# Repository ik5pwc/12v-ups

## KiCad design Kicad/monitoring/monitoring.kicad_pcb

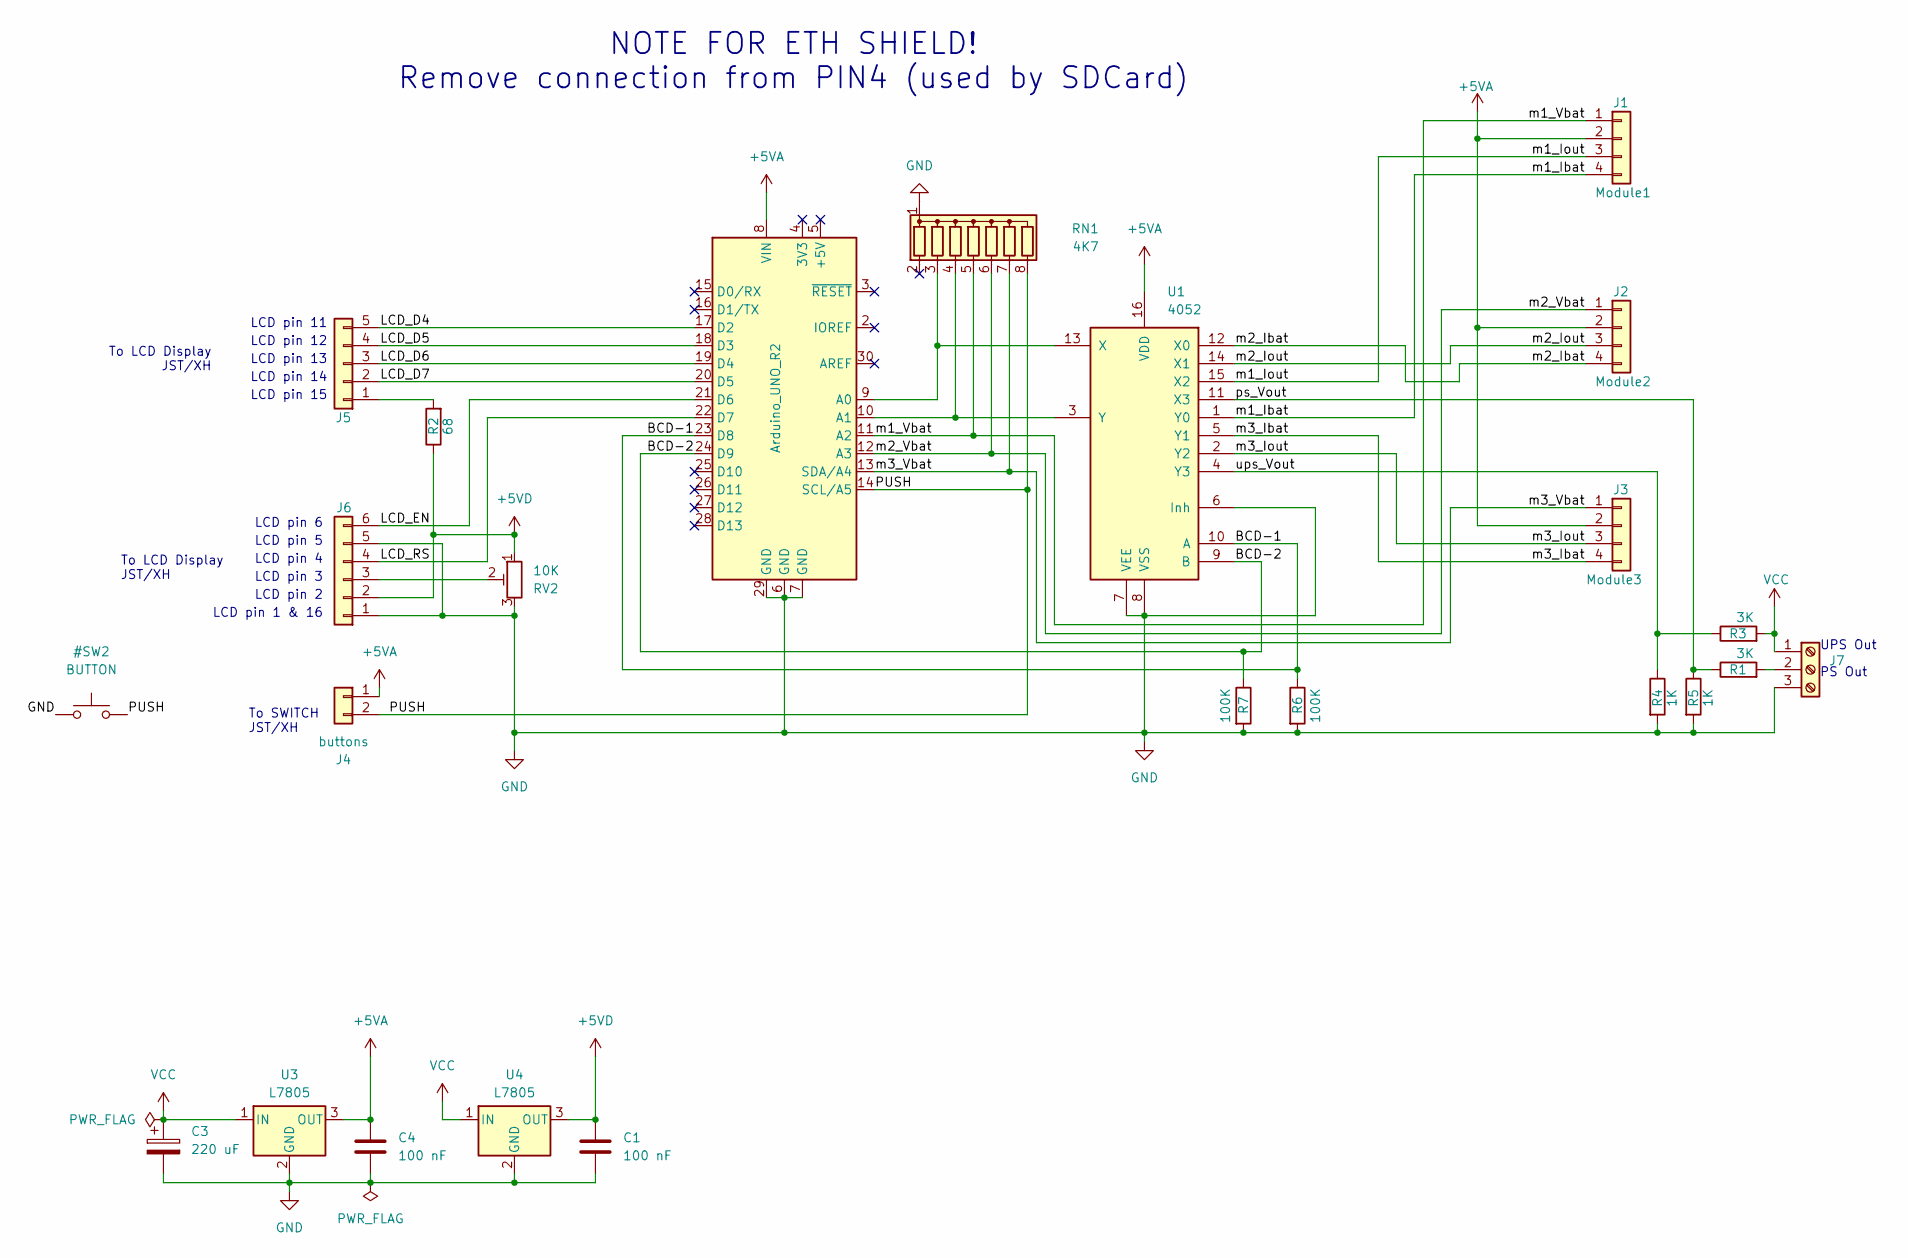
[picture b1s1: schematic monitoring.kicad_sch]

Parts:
A1: Arduino_UNO_R2
C1, C4: 100 nF; C_Disc_D4.7mm_W2.5mm_P5.00mm
C3: 220 uF; CP_Radial_D10.0mm_P5.00mm
J1: Module1; JST_XH_B4B-XH-A_1x04_P2.50mm_Vertical
J2: Module2; JST_XH_B4B-XH-A_1x04_P2.50mm_Vertical
J3: Module3; JST_XH_B4B-XH-A_1x04_P2.50mm_Vertical
J4: buttons; JST_XH_B2B-XH-A_1x02_P2.50mm_Vertical
J5: Display; JST_XH_B5B-XH-A_1x05_P2.50mm_Vertical
J6: Display; JST_XH_B6B-XH-A_1x06_P2.50mm_Vertical
J7: DC_in_outout; TerminalBlock_bornier-3_P5.08mm
R1, R3: 3K; R_Axial_DIN0204_L3.6mm_D1.6mm_P7.62mm_Horizontal
R2: 68; R_Axial_DIN0204_L3.6mm_D1.6mm_P7.62mm_Horizontal
R4, R5: 1K; R_Axial_DIN0204_L3.6mm_D1.6mm_P7.62mm_Horizontal
R6, R7: 100K; R_Axial_DIN0204_L3.6mm_D1.6mm_P7.62mm_Horizontal
RN1: 4K7; R_Array_SIP8
RV2: 10K; Potentiometer_Bourns_3296W_Vertical
U1: 4052; DIP-16_W7.62mm_LongPads
U3, U4: L7805; TO-220-3_Vertical

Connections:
+5VA: A1.8 (VIN), C4.1, J1.2, J2.2, J3.2, J4.1, U1.16 (VDD), U3.3 (OUT)
+5VD: C1.1, J6.2, R2.1, RV2.1, U4.3 (OUT)
/BCD-1: A1.23 (D8), R6.1, U1.10 (A)
/BCD-2: A1.24 (D9), R7.1, U1.9 (B)
/LCD_D4: A1.17 (D2), J5.5
/LCD_D5: A1.18 (D3), J5.4
/LCD_D6: A1.19 (D4), J5.3
/LCD_D7: A1.20 (D5), J5.2
/LCD_EN: A1.21 (D6), J6.6
/LCD_RS: A1.22 (D7), J6.4
/PUSH: A1.14 (SCL/A5), J4.2, RN1.8 (R7)
/m1_Ibat: J1.4, U1.1 (Y0)
/m1_Iout: J1.3, U1.15 (X2)
/m1_Vbat: A1.11 (A2), J1.1, RN1.5 (R4)
/m2_Ibat: J2.4, U1.12 (X0)
/m2_Iout: J2.3, U1.14 (X1)
/m2_Vbat: A1.12 (A3), J2.1, RN1.6 (R5)
/m3_Ibat: J3.4, U1.5 (Y1)
/m3_Iout: J3.3, U1.2 (Y2)
/m3_Vbat: A1.13 (SDA/A4), J3.1, RN1.7 (R6)
/ps_Vout: R1.1, R5.1, U1.11 (X3)
/ups_Vout: R3.1, R4.1, U1.4 (Y3)
GND: A1.6 (GND), A1.7 (GND), A1.29 (GND), C1.2, C3.2, C4.2, J6.1, J6.5, J7.3, R4.2, R5.2, R6.2, R7.2, RN1.1 (common), RV2.3, U1.6 (Inh), U1.7 (VEE), U1.8 (VSS), U3.2 (GND), U4.2 (GND)
unnamed: A1.9 (A0), RN1.3 (R2), U1.13 (X)
unnamed: A1.10 (A1), RN1.4 (R3), U1.3 (Y)
unnamed: J5.1, R2.2
unnamed: J6.3, RV2.2
unnamed: J7.2, R1.2
VCC: C3.1, J7.1, R3.2, U3.1 (IN), U4.1 (IN)

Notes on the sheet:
LCD pin 13
LCD pin 3
UPS Out
NOTE FOR ETH SHIELD! Remove connection from PIN4 (used by SDCard)
LCD pin 11
LCD pin 15
To SWITCH JST/XH
LCD pin 14
To LCD Display JST/XH
LCD pin 1 & 16
LCD pin 12
LCD pin 5
LCD pin 4
LCD pin 6
LCD pin 2
PS Out

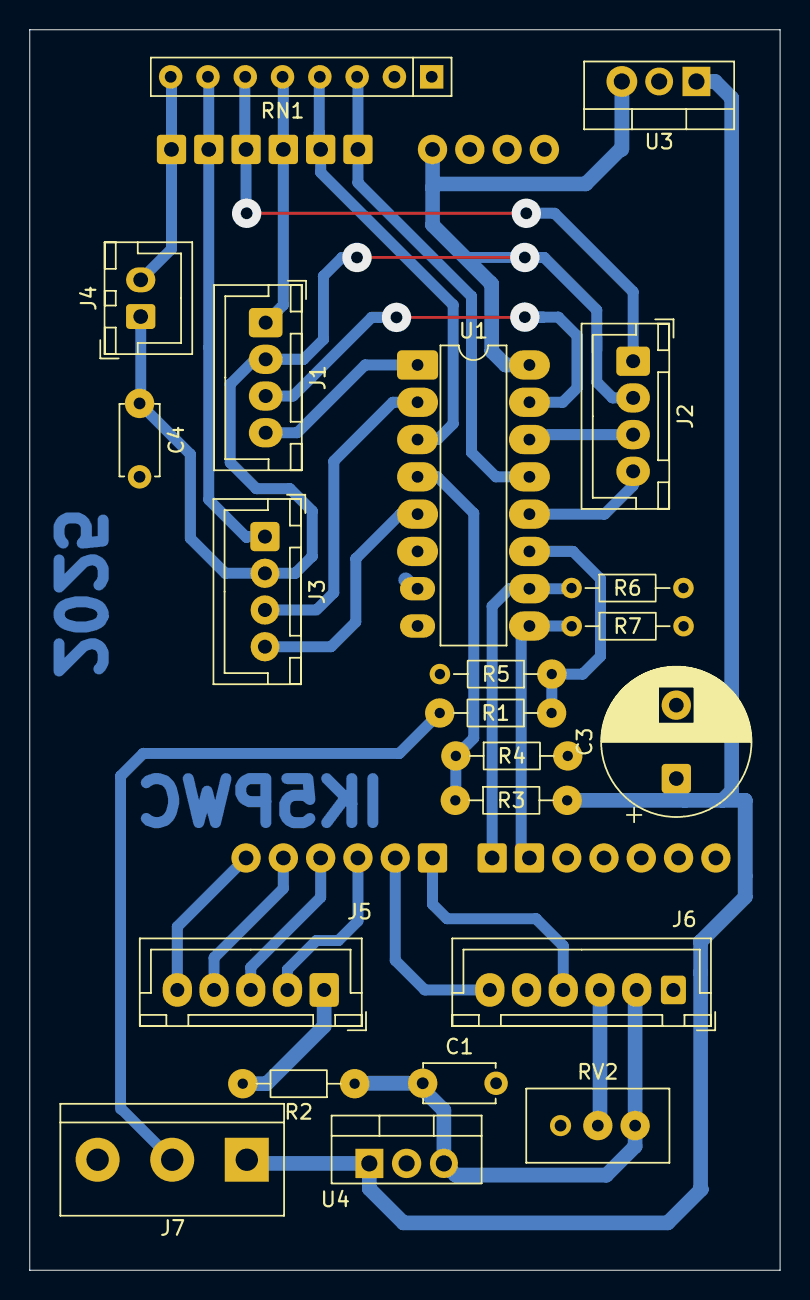
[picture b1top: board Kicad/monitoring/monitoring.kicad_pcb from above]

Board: 2 copper layers, 51.1 x 84.5 mm, 23 parts (1 on the bottom side), 29 nets.

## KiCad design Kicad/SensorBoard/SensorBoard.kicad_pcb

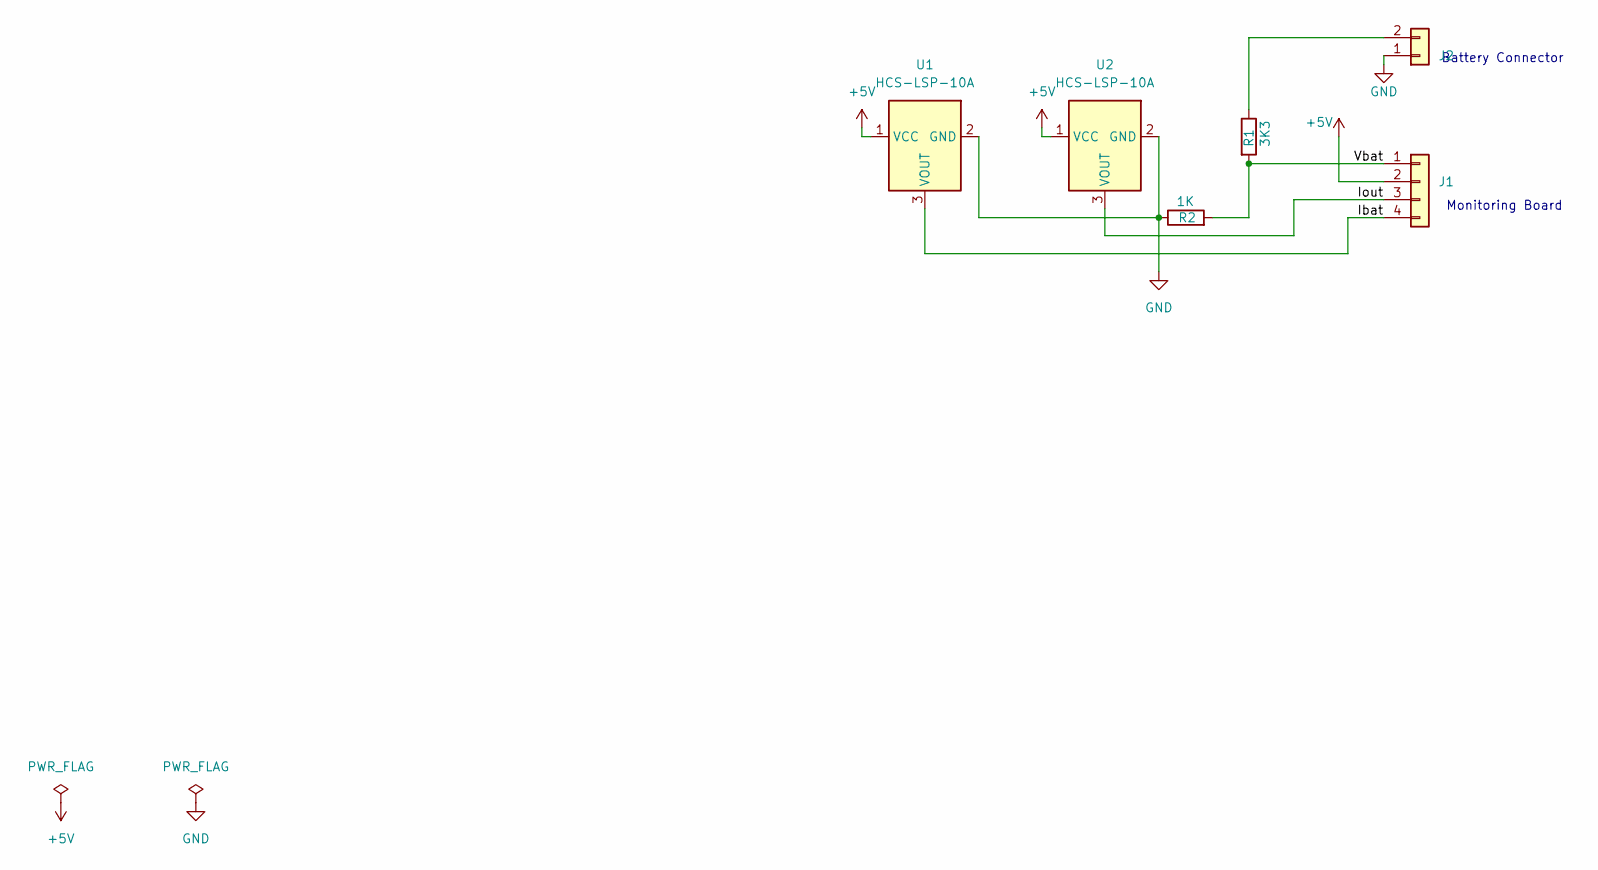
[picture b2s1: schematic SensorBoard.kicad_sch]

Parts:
J1: Conn_01x04; JST_XH_B4B-XH-A_1x04_P2.50mm_Vertical
J2: Conn_01x02; Mammooth_4mm
R1: 3K3; R_Axial_DIN0204_L3.6mm_D1.6mm_P7.62mm_Horizontal
R2: 1K; R_Axial_DIN0204_L3.6mm_D1.6mm_P7.62mm_Horizontal
U1, U2: HCS-LSP-10A; HCS-LSP

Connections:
+5V: J1.2, U1.1 (VCC), U2.1 (VCC)
/Ibat: J1.4, U1.3 (VOUT)
/Iout: J1.3, U2.3 (VOUT)
/Vbat: J1.1, R1.2, R2.2
GND: J2.1, R2.1, U1.2 (GND), U2.2 (GND)
unnamed: J2.2, R1.1

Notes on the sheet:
Monitoring Board
Battery Connector

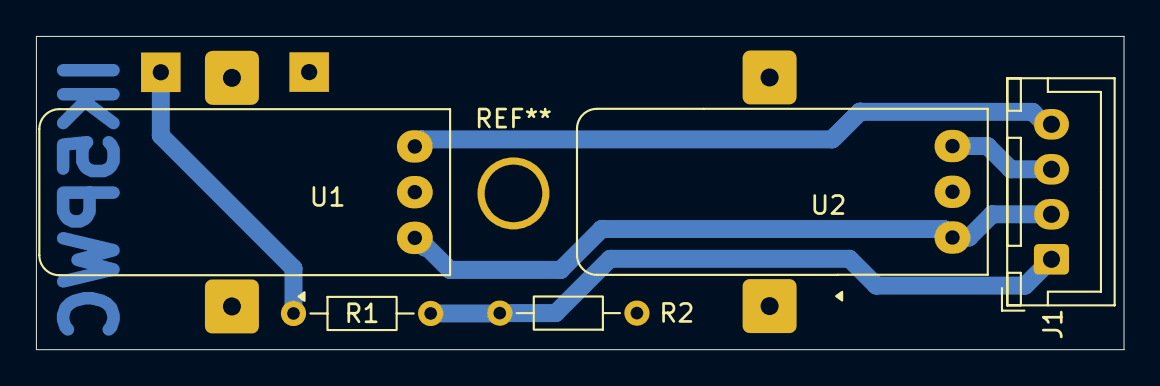
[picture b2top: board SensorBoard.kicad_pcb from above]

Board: 2 copper layers, 60.4 x 17.4 mm, 6 parts (0 on the bottom side), 6 nets.

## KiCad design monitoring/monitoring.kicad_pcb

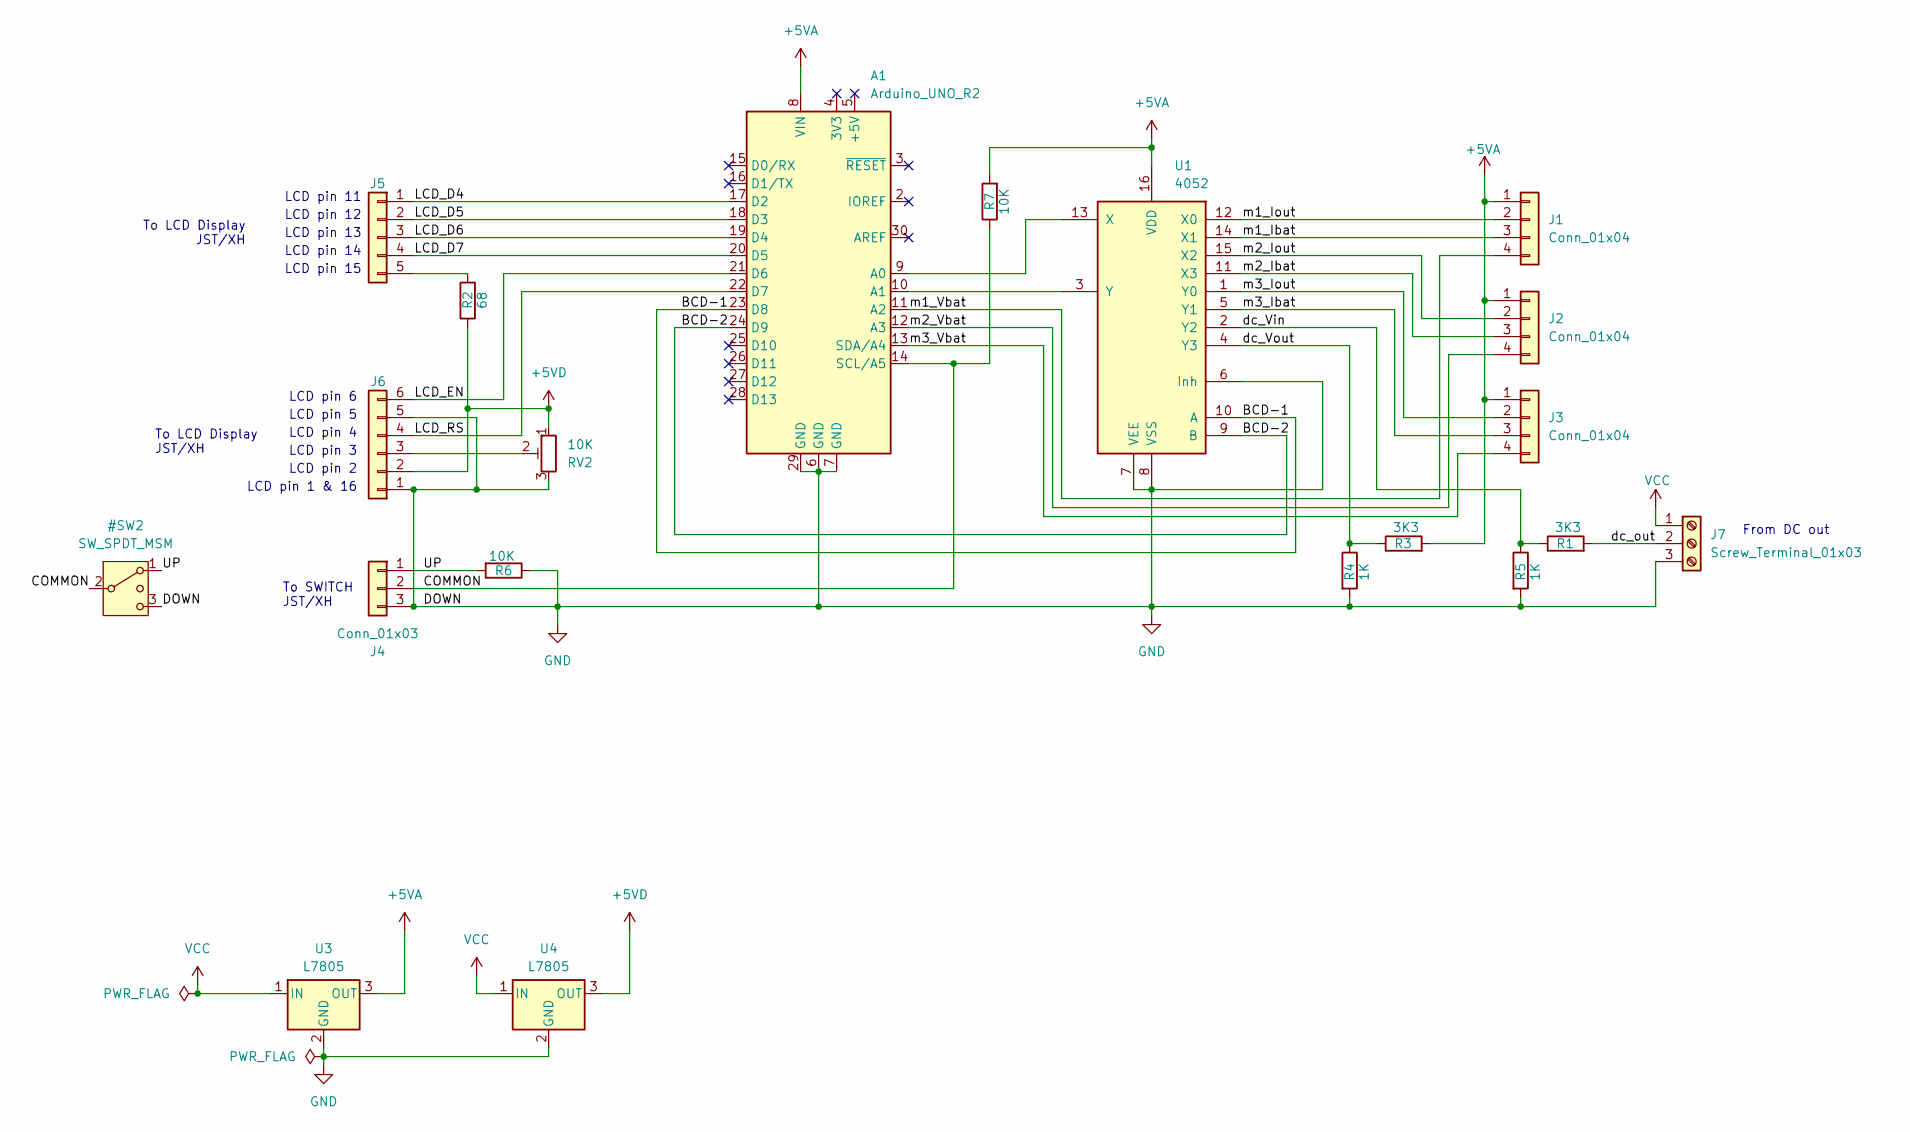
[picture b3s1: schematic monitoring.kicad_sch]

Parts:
A1: Arduino_UNO_R2
J1, J2, J3: Conn_01x04; JST_XH_B4B-XH-A_1x04_P2.50mm_Vertical
J4: Conn_01x03; JST_XH_B3B-XH-A_1x03_P2.50mm_Vertical
J5: Conn_01x05; JST_XH_B5B-XH-A_1x05_P2.50mm_Vertical
J6: Conn_01x05; JST_XH_B6B-XH-A_1x06_P2.50mm_Vertical
J7: Screw_Terminal_01x03; TerminalBlock_bornier-3_P5.08mm
R1, R3: 3K3; R_Axial_DIN0204_L3.6mm_D1.6mm_P7.62mm_Horizontal
R2: 68; R_Axial_DIN0204_L3.6mm_D1.6mm_P7.62mm_Horizontal
R4, R5: 1K; R_Axial_DIN0204_L3.6mm_D1.6mm_P7.62mm_Horizontal
R6, R7: 10K; R_Axial_DIN0204_L3.6mm_D1.6mm_P7.62mm_Horizontal
RV2: 10K; Potentiometer_Bourns_3296W_Vertical
U1: 4052; DIP-16_W7.62mm_LongPads
U3, U4: L7805; TO-220-3_Vertical

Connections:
+5VA: A1.8 (VIN), J1.1, J2.1, J3.1, R3.2, R7.2, U1.16 (VDD), U3.3 (OUT)
+5VD: J6.2, R2.1, RV2.1, U4.3 (OUT)
/BCD-1: A1.23 (D8), U1.10 (A)
/BCD-2: A1.24 (D9), U1.9 (B)
/LCD_D4: A1.17 (D2), J5.1
/LCD_D5: A1.18 (D3), J5.2
/LCD_D6: A1.19 (D4), J5.3
/LCD_D7: A1.20 (D5), J5.4
/LCD_EN: A1.21 (D6), J6.6
/LCD_RS: A1.22 (D7), J6.4
/dc_Vin: R1.1, R5.1, U1.2 (Y2)
/dc_Vout: R3.1, R4.1, U1.4 (Y3)
/dc_out: J7.2, R1.2
/m1_Ibat: J1.3, U1.14 (X1)
/m1_Iout: J1.2, U1.12 (X0)
/m1_Vbat: A1.11 (A2), J1.4
/m2_Ibat: J2.3, U1.11 (X3)
/m2_Iout: J2.2, U1.15 (X2)
/m2_Vbat: A1.12 (A3), J2.4
/m3_Ibat: J3.3, U1.5 (Y1)
/m3_Iout: J3.2, U1.1 (Y0)
/m3_Vbat: A1.13 (SDA/A4), J3.4
unnamed: A1.9 (A0), U1.13 (X)
unnamed: A1.10 (A1), U1.3 (Y)
unnamed: J5.5, R2.2
unnamed: J6.3, RV2.2
VCC: J7.1, U3.1 (IN), U4.1 (IN)

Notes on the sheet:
LCD pin 13
LCD pin 3
LCD pin 11
LCD pin 15
To SWITCH JST/XH
LCD pin 14
To LCD Display JST/XH
LCD pin 1 & 16
LCD pin 12
LCD pin 5
LCD pin 4
LCD pin 6
LCD pin 2
From DC out

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
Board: 2 copper layers, 19 parts (0 on the bottom side), 30 nets, no tracks yet.

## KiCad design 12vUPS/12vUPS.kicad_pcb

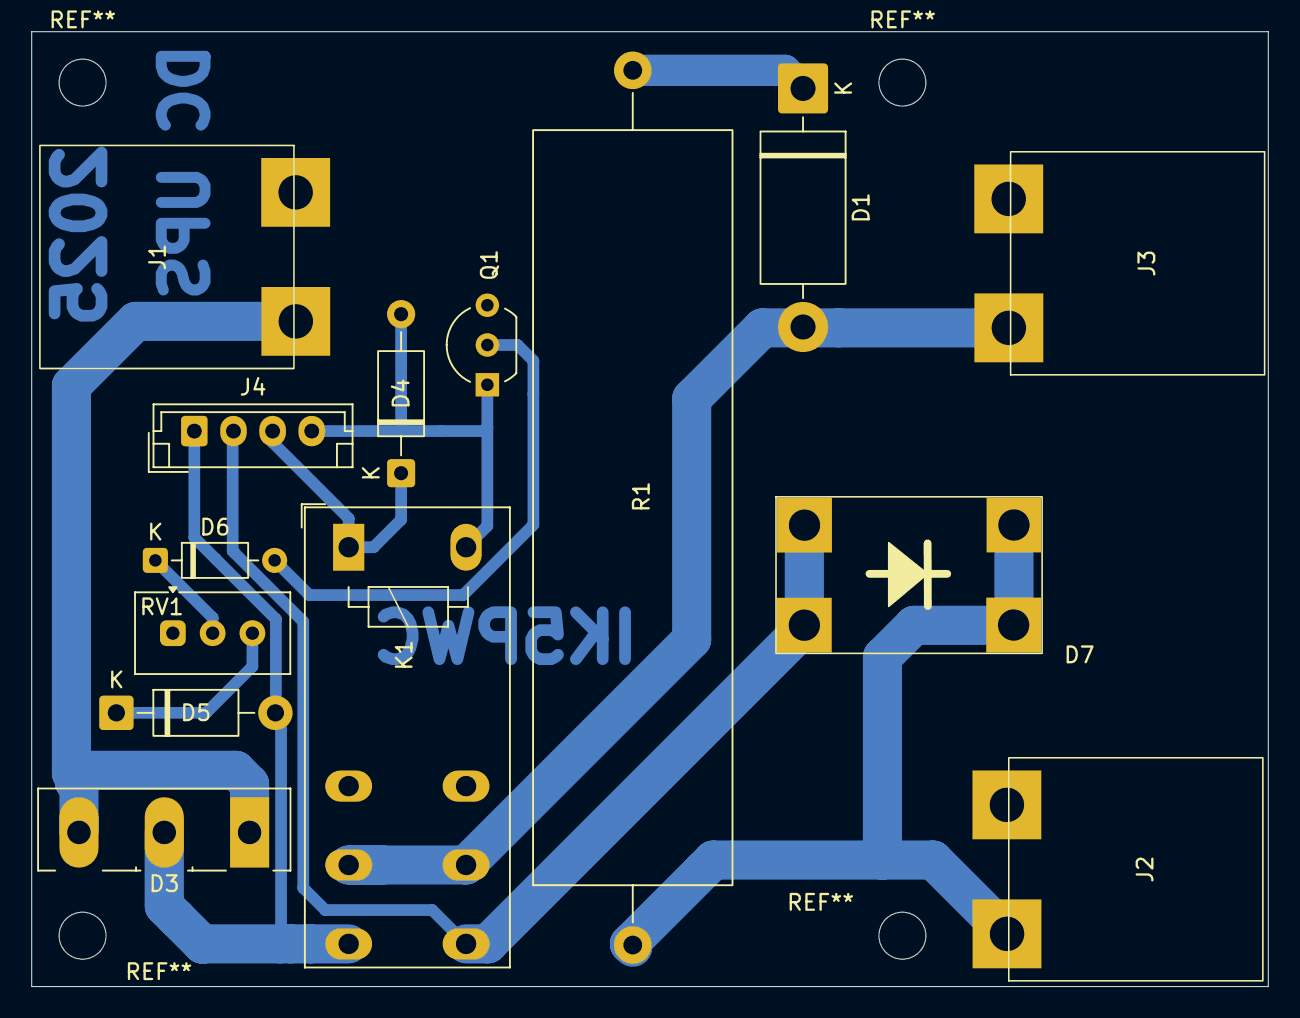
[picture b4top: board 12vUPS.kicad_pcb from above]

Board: 2 copper layers, 79.0 x 61.0 mm, 14 parts (0 on the bottom side), 12 nets.

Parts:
D1: SF30GG; D_DO-201AD_P15.24mm_Horizontal
D3: 60CPQ150; TO-247-3_Vertical
D4: 1N4001; D_A-405_P10.16mm_Horizontal
D5: D; D_DO-41_SOD81_P10.16mm_Horizontal
D6: 4V1; D_DO-35_SOD27_P7.62mm_Horizontal
D7: D_Ideal; D_IDEAL_no_GND
J1: INPUT; Mammooth_4mm
J2: BATTERY; Mammooth_4mm
J3: OUTPUT; Mammooth_4mm
J4: ENABLE; JST_EH_B4B-EH-A_1x04_P2.50mm_Vertical
K1: VEGHA L08A0212VDC; VEGhA L08 12V dc
Q1: BC337; TO-92_Inline_Wide
R1: 2R7; R_Axial_Power_L48.0mm_W12.5mm_P55.88mm
RV1: 10K; Potentiometer_Vishay_T93YA_Vertical

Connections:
/BATT_IN: D7.2 (A), J2.1, R1.1
/BJT-GND: D4.2 (A), J4.4, K1.A2, Q1.1 (C)
/DC-IN-RELE: D3.2 (K), D5.2 (A), J4.1, K1.14
/DC_IN: D3.1 (A), D3.3 (A), J1.2
/ENA: D4.1 (K), J4.3, K1.A1
/OUT: D1.2 (A), J3.1, K1.11, K1.21
GND: J1.1, J2.2, J3.2, Q1.3 (E), RV1.1
unnamed: D1.1 (K), R1.2
unnamed: D5.1 (K), RV1.3
unnamed: D6.2 (A), Q1.2 (B)
unnamed: D6.1 (K), RV1.2
unnamed: D7.1 (K), J4.2, K1.24

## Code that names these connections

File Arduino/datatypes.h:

/* ---------------------------------------------------------------------------------------
 * File        : datatypes.h
 * Author      : Civinini Luca - IK5PWC
 *               luca@ik5pwc.it
 *               http://www.ik5pwc.it
 *
 * Description : This .h file contains custom data types used within the project.
 * ---------------------------------------------------------------------------------------
*/


// Define guard for this file
#ifndef dt_h
#define dt_h

// Include arduino header
#include <Arduino.h>
#include "params.h"



/* ----------------------------------------------------------------------------------------------------------------
 *                                                ENUMs
 * ----------------------------------------------------------------------------------------------------------------
*/

// Define how IP address was assigned to device
enum dhcp_status_t : uint8_t {
  manual     = 0xA0,
  dynamic    = 0xA2,
	assigned   = 0xA4,
	fallback   = 0xA8
};


// Enum for button status
enum key_status_t : uint8_t {
  off     = 0x20,
  on      = 0x21,
};


/* ----------------------------------------------------------------------------------------------------------------
 *                                               STRUCTs
 * ----------------------------------------------------------------------------------------------------------------
*/

// all network-related stuff
struct network_t {
  uint8_t     ip[4]   = {0,0,0,0};      // Static or failback IP Address
  uint8_t     mask[4] = {0,0,0,0};      // Static or failback subnet mask
  uint8_t     gw[4]   = {0,0,0,0};      // Static or failback gateway
  uint8_t     mac[6]  = {0,0,0,0};      // Device mac address (computer on startup)
  dhcp_status_t  dhcp = dynamic;        // Track how the address was assigned
  uint16_t dhcp_timer = 0 ;             // DHCP Timer for rebind/renew
};


// Readings / scaling factor
struct dc_out_t {
	float m1_iout = 0;
	float m1_ibat = 0;
	float m1_vbat = 0;
	float m2_iout = 0;
	float m2_ibat = 0;
	float m2_vbat = 0;
	float m3_iout = 0;
	float m3_ibat = 0;
	float m3_vbat = 0;
	float ups_vout = 0;
	float ups_itot = 0;
	float ups_pwr = 0;
	float ps_vout = 0;
};


// Define custom debug
#if DEBUG
#define D_begin(...) Serial.begin(__VA_ARGS__);
#define D_print(...)    Serial.print(__VA_ARGS__)
#define D_write(...)    Serial.write(__VA_ARGS__)
#define D_println(...)  Serial.println(__VA_ARGS__)
#else
#define D_begin(...)
#define D_print(...)
#define D_write(...)
#define D_println(...)
#endif



// end of define guard
#endif

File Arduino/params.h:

/* ---------------------------------------------------------------------------------------
 * File        : params.h
 * Author      : Civinini Luca - IK5PWC
 *                 luca@civinini.net - http://www.civinini.net
 *                 luca@ik5pwc.it    - http://www.ik5pwc.it
 *
 * Description : This .h file contains all configurable parameters used in the project.
 *               It must be included in every .cpp/.h file
 * ---------------------------------------------------------------------------------------
*/


// Define guard for this file
#ifndef params_h
#define params_h


/* ----------------------------------------------------------------------------------------------------------------
 *                                             PARAMS CONFIGURATION STARTS
 * ----------------------------------------------------------------------------------------------------------------
 */

#define ENABLE_DHCP true                    /* true: use DHCP Server and failback to static if none available
                                             * false: use only static
                                             * NOTE: DHCP is probed periodically and assigned IP takes precedence
                                             * over failback one.
                                             */


const uint8_t static_ip[]   = {192,168,255,100};    // IP Address - used also as failback if DHCP is unavailable
const uint8_t static_mask[] = {255,255,255,100};    // Subnet mask - used also as failback if DHCP is unavailable
const uint8_t static_gw[]   = {192,168,255,1};      // Gateway - used also as failback if DHCP is unavailable


// Define where server will listen
#define PORT 23


// Input LCD pins
// Uses 4 pin (i.e. 4 bit nibble)
#define LCD_D4 2                    // LCD Data 4
#define LCD_D5 3                    // LCD Data 5
#define LCD_D6 4                    // LCD Data 6
#define LCD_D7 5                    // LCD Data 7
#define LCD_EN 6                    // LCD Definition - Enable PIN
#define LCD_RS 7                    // LCD Definition - R/S PIN

// LCD size
#define LCD_COLS 16                 // number of columns (min 16)
#define PAGE_TIMEOUT_SEC 30         // how many seconds remains in specific lcd page (max 250 sec)

#define DATA_REFRESH 4              // how often refresh data to lcd, telnet or MQTT (min 3, max 250 sec)


// Scaling factors for readings - adjust based on resistor values and current sensos
#define ADC_ERR_VOLTAGE     30      // QTY to sum or subctract from ADC value to make it read right values (for voltages)
                                    // To be defined experimentally comparing ADC readout with input value

#define ADC_ERR_CURRENT     15      // QTY to sum or subctract from ADC value to make it read right values (for current)
                                    // To be defined experimentally comparing ADC readout with input value

#define CURRENT_SENSOR_MAX  10      // Max current reading for specified sensor

#define SCALE_VOLTAGE       4.15    // Based on voltage partition formula + experimental adj
                                    // Compare input voltage with one from partition

// Used if current sensor is place reversed regarding current flow
#define SCALE_M1_IOUT  -1           // Module 1: Load Current
#define SCALE_M1_IBAT  -1           // Module 1: Battery Current
#define SCALE_M2_IOUT  -1           // Module 2: Load Current (reverse)
#define SCALE_M2_IBAT  -1           // Module 2: Battery Current
#define SCALE_M3_IOUT  -1           // Module 3: Load Current
#define SCALE_M3_IBAT  -1           // Module 3: Battery Current

// Switch buttons
#define BUTTON   A5                 // Button PIN

// Output PIN dor driving multiplexer
#define AMUX1 8                     // Multiplexer A pin
#define AMUX2 9                     // Multiplexer B pin


#define MQTTSUPPORT  1              // Set to 1 to enable MQTT

// MQTT Broker settings
#define MQTTBROKER   "192.168.95.6"
#define MQTTPORT     1883

// MQTT Root topic & client ID
#define MQTTTOPIC    "home/net/dcups"
#define MQTTCLIENTID "net-dc-ups"



/* ----------------------------------------------------------------------------------------------------------------
 *                                              PARAMS CONFIGURATION END
 * ----------------------------------------------------------------------------------------------------------------
 */



#define VERSION "1.1"               // Program version

// end of define guard
#endif

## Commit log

2025-06-02 Update 12vUPS-2025-06-02_174418.zip, 12vUPS-2025-06-02_175555.zip, 12vUPS-2025-06-02_180136.zip, and 8 more files
2025-06-06 Update 12vUPS-2025-06-02_174418.zip, 12vUPS-2025-06-06_223532.zip, 12vUPS-2025-06-06_224038.zip, and 9 more files
2025-06-07 Update #auto_saved_files#, 12vUPS-2025-06-06_223532.zip, 12vUPS-2025-06-07_150941.zip, and 13 more files
2025-06-08 Update #auto_saved_files#, 12vUPS-2025-06-07_150941.zip, 12vUPS-2025-06-07_151452.zip, and 15 more files
2025-06-10 Update 12vUPS-2025-06-08_110639.zip, 12vUPS-2025-06-08_231957.zip, 12vUPS-2025-06-08_232518.zip, and 11 more files
2025-06-10 Update 12vUPS-2025-06-10_185612.zip, 12vUPS-2025-06-10_190121.zip, 12vUPS-2025-06-10_190645.zip, and 3 more files
2025-06-13 Update #auto_saved_files#, 12vUPS-2025-06-02_175555.zip, 12vUPS-2025-06-02_180136.zip, and 18 more files
2025-06-20 Update 12vUPS-2025-06-06_224542.zip, 12vUPS-2025-06-06_225111.zip, 12vUPS-2025-06-06_225614.zip, and 28 more files
2025-06-20 Update #auto_saved_files#, 12vUPS.kicad_prl, _autosave-12vUPS.kicad_sch, and 2 more files
2025-06-22 Update .~lock.12vUPS.csv#, 12vUPS-2025-06-08_232518.zip, 12vUPS-2025-06-08_233102.zip, and 4 more files
2025-06-22 Update 12vUPS-2025-06-08_233608.zip, 12vUPS-2025-06-08_234122.zip, 12vUPS-2025-06-22_122202.zip, and 5 more files
2025-06-27 Update .~lock.12vUPS.csv#, 12vUPS-2025-06-10_185612.zip, 12vUPS-2025-06-10_190121.zip, and 11 more files
2025-07-06 Update .cproject, .gitignore, .project, and 8 more files
2025-07-10 Update UPSMonitor.ino, datatypes.h, network.cpp, and 2 more files
2025-07-13 Update UPSMonitor.ino, datatypes.h, network.cpp, and 1 more file
2025-07-13 Update 12vUPS.kicad_pro, 12vUPS.kicad_sch, Sensor.kicad_sch, and 2 more files
2025-07-13 Update 12vUPS-2025-06-13_190822.zip, 12vUPS-2025-06-13_191335.zip, 12vUPS-2025-06-13_192019.zip, and 5 more files
2025-07-14 Update 12vUPS-modles.kicad_prl, 12vUPS-modules-2025-07-13_234921.zip, 12vUPS-modules-2025-07-14_221001.zip, and 54 more files
2025-07-17 Update 12vUPS-modles.kicad_prl, 12vUPS-modules-2025-07-13_234921.zip, 12vUPS-modules-2025-07-14_221001.zip, and 69 more files
2025-07-17 Update #auto_saved_files#, Arduino_UNO_R2.kicad_mod, fp-info-cache, and 9 more files
2025-07-17 Ready for 1st test
2025-07-22 Update .cproject, .project, UPSMonitor.ino, and 29 more files
2025-07-22 Update UPSMonitor.ino, datatypes.h, io.cpp, and 18 more files
2025-07-22 Update UPSMonitor.eep, UPSMonitor.elf, UPSMonitor.hex, and 90 more files
2025-07-25 Update .sproject, io.cpp, io.h, and 29 more files
2025-07-25 Update 12vUPS-2025-07-25_155804.zip, #auto_saved_files#, 12vUPS-2025-06-08_233102.zip, and 32 more files
2025-07-26 Test con MQTT
2025-07-27 Update .cproject, .project, .sproject, and 7 more files
2025-07-27 Completed MQTT support
2025-08-01 Update .sproject, params.h, SensorBoard-2025-07-29_231028.zip, and 10 more files
2025-08-01 Update fp-info-cache, monitoring-2025-07-18_201733.zip, monitoring-2025-07-18_212227.zip, and 5 more files
